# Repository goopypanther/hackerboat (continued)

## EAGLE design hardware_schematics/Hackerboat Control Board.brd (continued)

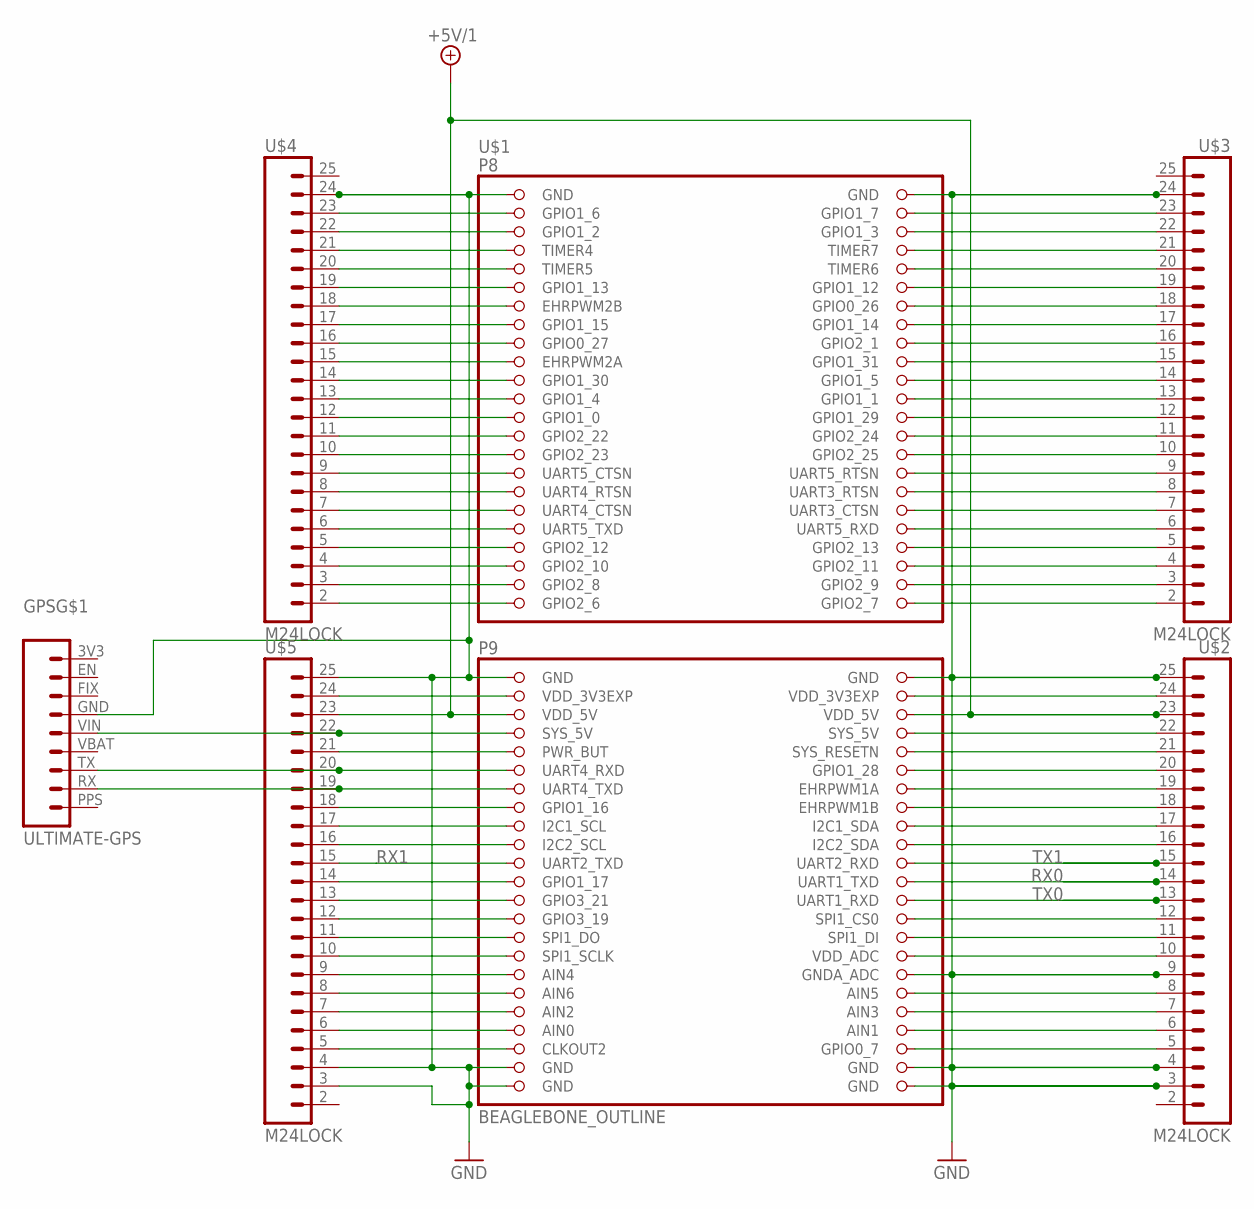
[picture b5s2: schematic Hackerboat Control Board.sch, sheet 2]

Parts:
GPS: ULTIMATE-GPS
U$1: BEAGLEBONE_OUTLINE; BEAGLEBONE_SHIELD
U$2, U$3, U$4, U$5: M24LOCK; 1X24_LOCK

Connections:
+5V/1: U$1.51 (VDD_5V), U$1.52 (VDD_5V), U$2.23, U$5.23; also elsewhere on the board
GND: GPS.GND (6), U$1.1 (GND), U$1.2 (GND), U$1.47 (GND), U$1.48 (GND), U$1.80 (GNDA_ADC), U$1.89 (GND), U$1.90 (GND), U$1.91 (GND), U$1.92 (GND), U$2.3, U$2.4, U$2.9, U$2.25, U$3.24, U$4.24, U$5.3, U$5.4, U$5.25; also elsewhere on the board
unnamed: GPS.RX (2), U$1.59 (UART4_TXD), U$5.19
unnamed: GPS.TX (3), U$1.57 (UART4_RXD), U$5.20
unnamed: GPS.VIN (5), U$1.53 (SYS_5V), U$5.22
unnamed: U$1.49 (VDD_3V3EXP), U$5.24
unnamed: U$1.88 (GPIO0_7), U$2.5
unnamed: U$1.86 (AIN1), U$2.6
unnamed: U$1.84 (AIN3), U$2.7
unnamed: U$1.82 (AIN5), U$2.8
unnamed: U$1.78 (VDD_ADC), U$2.10
unnamed: U$1.76 (SPI1_DI), U$2.11
unnamed: U$1.74 (SPI1_CS0), U$2.12
unnamed: U$1.66 (I2C2_SDA), U$2.16
unnamed: U$1.64 (I2C1_SDA), U$2.17
unnamed: U$1.62 (EHRPWM1B), U$2.18
unnamed: U$1.60 (EHRPWM1A), U$2.19
unnamed: U$1.58 (GPIO1_28), U$2.20
unnamed: U$1.56 (SYS_RESETN), U$2.21
unnamed: U$1.54 (SYS_5V), U$2.22
unnamed: U$1.50 (VDD_3V3EXP), U$2.24
unnamed: U$1.46 (GPIO2_7), U$3.2
unnamed: U$1.44 (GPIO2_9), U$3.3
unnamed: U$1.42 (GPIO2_11), U$3.4
unnamed: U$1.40 (GPIO2_13), U$3.5
unnamed: U$1.38 (UART5_RXD), U$3.6
unnamed: U$1.36 (UART3_CTSN), U$3.7
unnamed: U$1.34 (UART3_RTSN), U$3.8
unnamed: U$1.32 (UART5_RTSN), U$3.9
unnamed: U$1.30 (GPIO2_25), U$3.10
unnamed: U$1.28 (GPIO2_24), U$3.11
unnamed: U$1.26 (GPIO1_29), U$3.12
unnamed: U$1.24 (GPIO1_1), U$3.13
unnamed: U$1.22 (GPIO1_5), U$3.14
unnamed: U$1.20 (GPIO1_31), U$3.15
unnamed: U$1.18 (GPIO2_1), U$3.16
unnamed: U$1.16 (GPIO1_14), U$3.17
unnamed: U$1.14 (GPIO0_26), U$3.18
unnamed: U$1.12 (GPIO1_12), U$3.19
unnamed: U$1.10 (TIMER6), U$3.20
unnamed: U$1.8 (TIMER7), U$3.21
unnamed: U$1.6 (GPIO1_3), U$3.22
unnamed: U$1.4 (GPIO1_7), U$3.23
unnamed: U$1.45 (GPIO2_6), U$4.2
unnamed: U$1.43 (GPIO2_8), U$4.3
unnamed: U$1.41 (GPIO2_10), U$4.4
unnamed: U$1.39 (GPIO2_12), U$4.5
unnamed: U$1.37 (UART5_TXD), U$4.6
unnamed: U$1.35 (UART4_CTSN), U$4.7
unnamed: U$1.33 (UART4_RTSN), U$4.8
unnamed: U$1.31 (UART5_CTSN), U$4.9
unnamed: U$1.29 (GPIO2_23), U$4.10
unnamed: U$1.27 (GPIO2_22), U$4.11
unnamed: U$1.25 (GPIO1_0), U$4.12
unnamed: U$1.23 (GPIO1_4), U$4.13
unnamed: U$1.21 (GPIO1_30), U$4.14
unnamed: U$1.19 (EHRPWM2A), U$4.15
unnamed: U$1.17 (GPIO0_27), U$4.16
unnamed: U$1.15 (GPIO1_15), U$4.17
unnamed: U$1.13 (EHRPWM2B), U$4.18
unnamed: U$1.11 (GPIO1_13), U$4.19
unnamed: U$1.9 (TIMER5), U$4.20
unnamed: U$1.7 (TIMER4), U$4.21
unnamed: U$1.5 (GPIO1_2), U$4.22
unnamed: U$1.3 (GPIO1_6), U$4.23
unnamed: U$1.87 (CLKOUT2), U$5.5
unnamed: U$1.85 (AIN0), U$5.6
unnamed: U$1.83 (AIN2), U$5.7
unnamed: U$1.81 (AIN6), U$5.8
unnamed: U$1.79 (AIN4), U$5.9
unnamed: U$1.77 (SPI1_SCLK), U$5.10
unnamed: U$1.75 (SPI1_DO), U$5.11
unnamed: U$1.73 (GPIO3_19), U$5.12
unnamed: U$1.71 (GPIO3_21), U$5.13
unnamed: U$1.69 (GPIO1_17), U$5.14
unnamed: U$1.65 (I2C2_SCL), U$5.16
unnamed: U$1.63 (I2C1_SCL), U$5.17
unnamed: U$1.61 (GPIO1_16), U$5.18
unnamed: U$1.55 (PWR_BUT), U$5.21
RX0: U$1.70 (UART1_TXD), U$2.14; also elsewhere on the board
RX1: U$1.67 (UART2_TXD), U$5.15; also elsewhere on the board
TX0: U$1.72 (UART1_RXD), U$2.13; also elsewhere on the board
TX1: U$1.68 (UART2_RXD), U$2.15; also elsewhere on the board

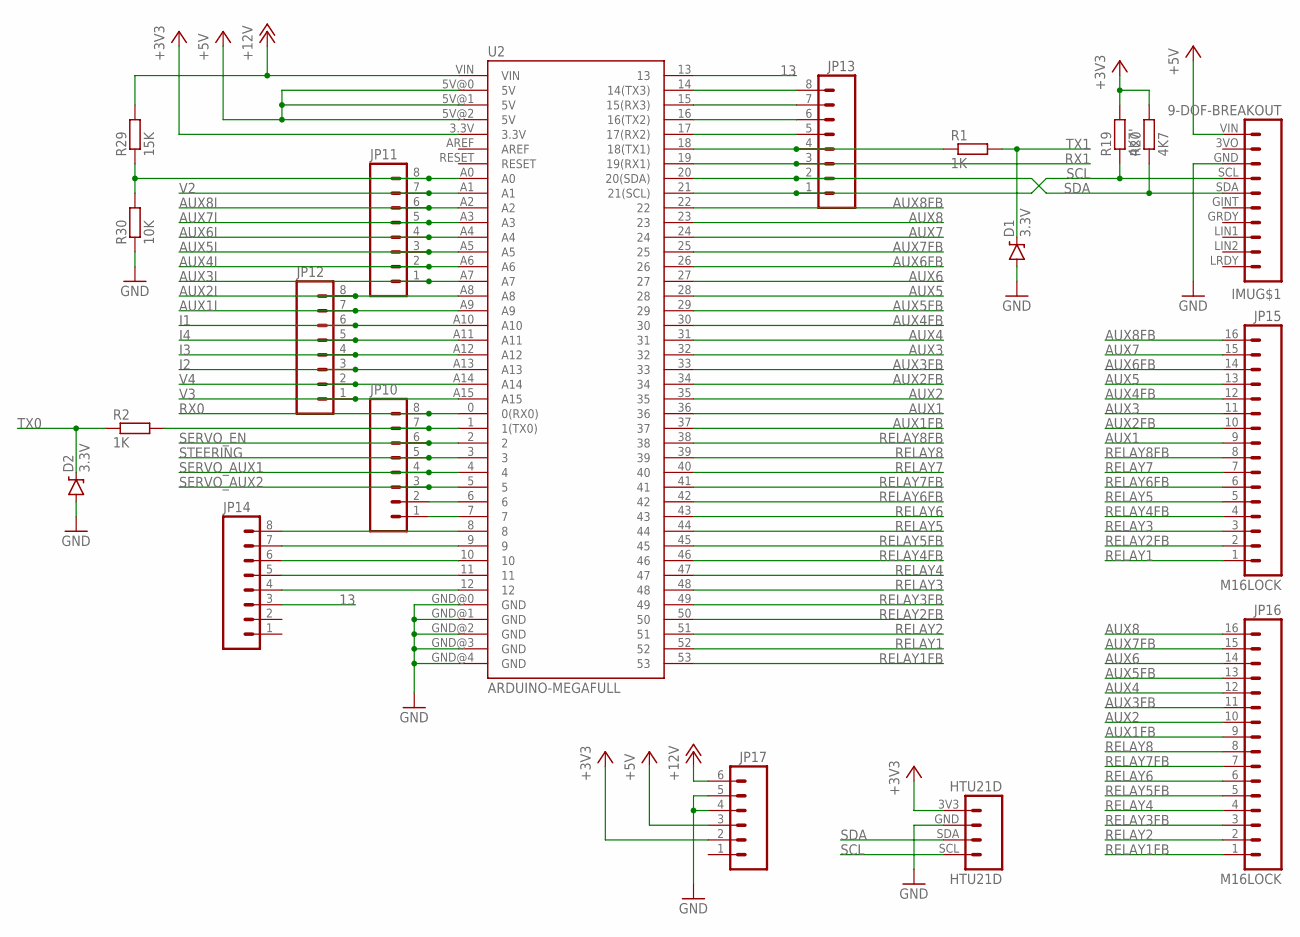
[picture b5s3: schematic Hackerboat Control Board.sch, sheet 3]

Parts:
D1, D2: 3.3V; SOD-323
HTU21D: HTU21D
IMU: 9-DOF-BREAKOUT
JP10, JP11, JP12, JP13, JP14: M08LOCK; 1X08_LOCK
JP15, JP16: M16LOCK; 1X16_LOCK
JP17: M06LOCK; 1X06_LOCK
R1, R2: 1K; R0603
R19: 4K7'; R0603
R20: 4K7; R0603
R29: 15K; R0603
R30: 10K; R0603
U2: ARDUINO-MEGAFULL; ARDUINO_MEGA

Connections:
13: JP14.3, U2.13
+3V3: HTU21D.3V3 (1), JP17.2, R19.2, R20.2, U2.3.3V
+5V: IMU.VIN (1), JP17.3, U2.5V@0 (5V), U2.5V@1 (5V), U2.5V@2 (5V); also elsewhere on the board
+12V: JP17.6, R29.2, U2.VIN; also elsewhere on the board
AUX1: JP15.9, U2.36; also elsewhere on the board
AUX1FB: JP16.9, U2.37; also elsewhere on the board
AUX1I: JP12.7, U2.A9; also elsewhere on the board
AUX2: JP16.10, U2.35; also elsewhere on the board
AUX2FB: JP15.10, U2.34; also elsewhere on the board
AUX2I: JP12.8, U2.A8; also elsewhere on the board
AUX3: JP15.11, U2.32; also elsewhere on the board
AUX3FB: JP16.11, U2.33; also elsewhere on the board
AUX3I: JP11.1, U2.A7; also elsewhere on the board
AUX4: JP16.12, U2.31; also elsewhere on the board
AUX4FB: JP15.12, U2.30; also elsewhere on the board
AUX4I: JP11.2, U2.A6; also elsewhere on the board
AUX5: JP15.13, U2.28; also elsewhere on the board
AUX5FB: JP16.13, U2.29; also elsewhere on the board
AUX5I: JP11.3, U2.A5; also elsewhere on the board
AUX6: JP16.14, U2.27; also elsewhere on the board
AUX6FB: JP15.14, U2.26; also elsewhere on the board
AUX6I: JP11.4, U2.A4; also elsewhere on the board
AUX7: JP15.15, U2.24; also elsewhere on the board
AUX7FB: JP16.15, U2.25; also elsewhere on the board
AUX7I: JP11.5, U2.A3; also elsewhere on the board
AUX8: JP16.16, U2.23; also elsewhere on the board
AUX8FB: JP15.16, U2.22; also elsewhere on the board
AUX8I: JP11.6, U2.A2; also elsewhere on the board
GND: D1.A, D2.A, HTU21D.GND (2), IMU.GND (3), JP17.4, JP17.5, R30.1, U2.GND@0 (GND), U2.GND@1 (GND), U2.GND@2 (GND), U2.GND@3 (GND), U2.GND@4 (GND); also elsewhere on the board
I1: JP12.6, U2.A10; also elsewhere on the board
I2: JP12.3, U2.A13; also elsewhere on the board
I3: JP12.4, U2.A12; also elsewhere on the board
I4: JP12.5, U2.A11; also elsewhere on the board
unnamed: JP13.4, R1.1, U2.18 (18(TX1))
unnamed: JP10.7, R2.2, U2.1 (1(TX0))
unnamed: JP10.1, U2.7
unnamed: JP10.2, U2.6
unnamed: JP11.8, R29.1, R30.2, U2.A0
unnamed: JP13.5, U2.17 (17(RX2))
unnamed: JP13.6, U2.16 (16(TX2))
unnamed: JP13.7, U2.15 (15(RX3))
unnamed: JP13.8, U2.14 (14(TX3))
unnamed: JP14.8, U2.8
unnamed: JP14.7, U2.9
unnamed: JP14.6, U2.10
unnamed: JP14.5, U2.11
unnamed: JP14.4, U2.12
RELAY1: JP15.1, U2.52; also elsewhere on the board
RELAY1FB: JP16.1, U2.53; also elsewhere on the board
RELAY2: JP16.2, U2.51; also elsewhere on the board
RELAY2FB: JP15.2, U2.50; also elsewhere on the board
RELAY3: JP15.3, U2.48; also elsewhere on the board
RELAY3FB: JP16.3, U2.49; also elsewhere on the board
RELAY4: JP16.4, U2.47; also elsewhere on the board
RELAY4FB: JP15.4, U2.46; also elsewhere on the board
RELAY5: JP15.5, U2.44; also elsewhere on the board
RELAY5FB: JP16.5, U2.45; also elsewhere on the board
RELAY6: JP16.6, U2.43; also elsewhere on the board
RELAY6FB: JP15.6, U2.42; also elsewhere on the board
RELAY7: JP15.7, U2.40; also elsewhere on the board
RELAY7FB: JP16.7, U2.41; also elsewhere on the board
RELAY8: JP16.8, U2.39; also elsewhere on the board
RELAY8FB: JP15.8, U2.38; also elsewhere on the board
RX0: JP10.8, U2.0 (0(RX0)); also elsewhere on the board
RX1: JP13.3, U2.19 (19(RX1)); also elsewhere on the board
SCL: HTU21D.SCL (4), IMU.SCL (4), JP13.1, R19.1, U2.21 (21(SCL))
SDA: HTU21D.SDA (3), IMU.SDA (5), JP13.2, R20.1, U2.20 (20(SDA))
SERVO_AUX1: JP10.4, U2.4; also elsewhere on the board
SERVO_AUX2: JP10.3, U2.5; also elsewhere on the board
SERVO_EN: JP10.6, U2.2; also elsewhere on the board
STEERING: JP10.5, U2.3; also elsewhere on the board
TX0: D2.C, R2.1; also elsewhere on the board
TX1: D1.C, R1.2; also elsewhere on the board
V2: JP11.7, U2.A1; also elsewhere on the board
V3: JP12.1, U2.A15; also elsewhere on the board
V4: JP12.2, U2.A14; also elsewhere on the board

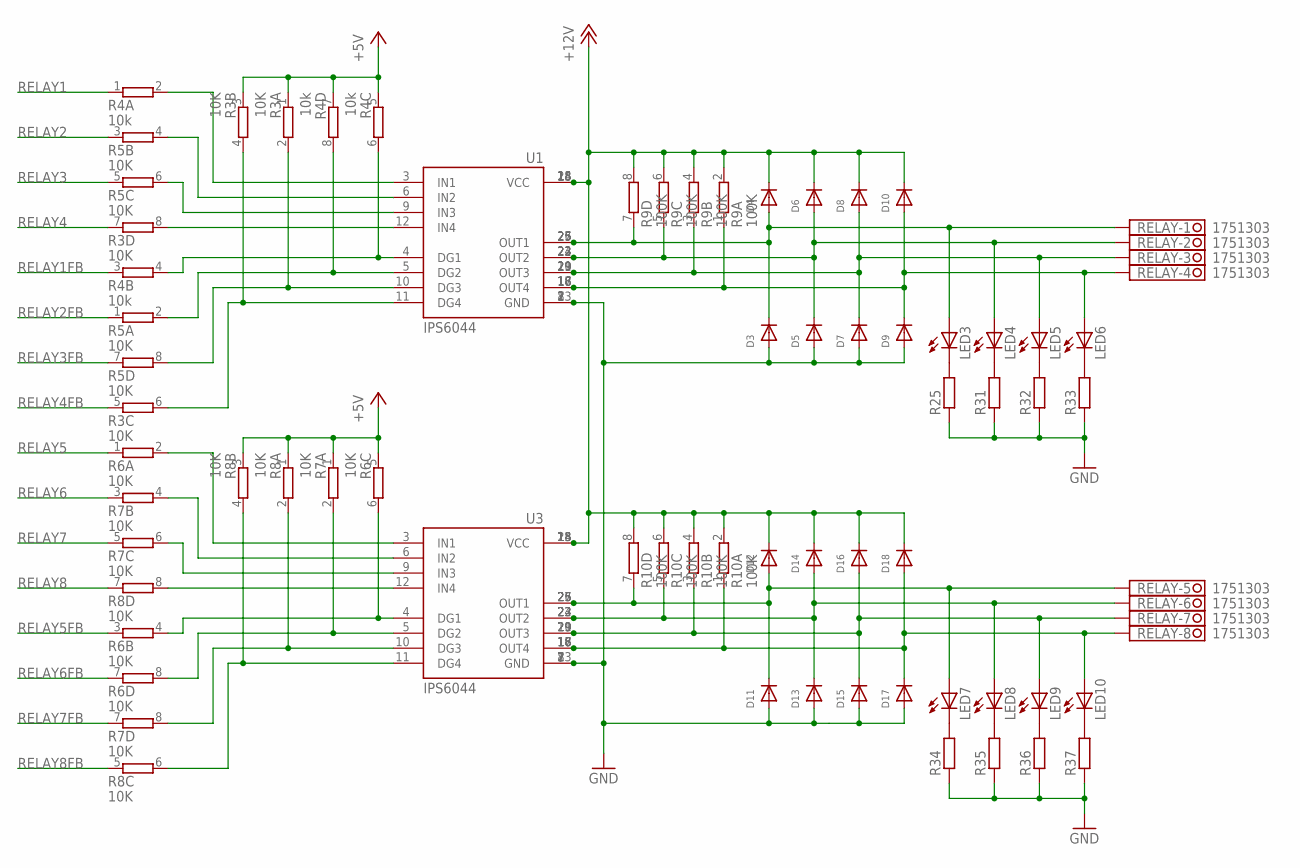
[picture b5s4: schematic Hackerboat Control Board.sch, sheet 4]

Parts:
D3, D4, D5, D6, D7, D8, D9, D10, D11, D12, D13, D14, D15, D16, D17, D18: DIODESOD-123; SOD-123
LED3, LED4, LED5, LED6, LED7, LED8, LED9, LED10: LEDCHIPLED_0805; CHIPLED_0805
R3, R5, R6, R7, R8: 10K; CTS742C083-RES
R4: 10k; CTS742C083-RES
R9, R10: 100K; CTS742C083-RES
R25, R31, R32, R33, R34, R35, R36, R37: R-EU_R0603; R0603
RELAY: 1751303
U1, U3: IPS6044; SO-28L

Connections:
+5V: R3.1, R3.3 (1), R4.5 (1), R4.7 (1), R6.5 (1), R7.1, R8.1, R8.3 (1); also elsewhere on the board
+12V: D4.C, D6.C, D8.C, D10.C, D12.C, D14.C, D16.C, D18.C, R9.2, R9.4 (2), R9.6 (2), R9.8 (2), R10.2, R10.4 (2), R10.6 (2), R10.8 (2), U1.1 (VCC), U1.14 (VCC), U1.15 (VCC), U1.28 (VCC), U3.1 (VCC), U3.14 (VCC), U3.15 (VCC), U3.28 (VCC); also elsewhere on the board
GND: D3.A, D5.A, D7.A, D9.A, D11.A, D13.A, D15.A, D17.A, R25.1, R31.1, R32.1, R33.1, R34.1, R35.1, R36.1, R37.1, U1.2 (GND), U1.7 (GND), U1.8 (GND), U1.13 (GND), U3.2 (GND), U3.7 (GND), U3.8 (GND), U3.13 (GND); also elsewhere on the board
unnamed: R6.2, U3.3 (IN1)
unnamed: R8.8 (2), U3.12 (IN4)
unnamed: R7.6 (2), U3.9 (IN3)
unnamed: D3.C, D4.A, LED3.A, R9.7 (1), RELAY.1, U1.25 (OUT1), U1.26 (OUT1), U1.27 (OUT1)
unnamed: D5.C, D6.A, LED4.A, R9.5 (1), RELAY.2, U1.22 (OUT2), U1.23 (OUT2), U1.24 (OUT2)
unnamed: D7.C, D8.A, LED5.A, R9.3 (1), RELAY.3, U1.19 (OUT3), U1.20 (OUT3), U1.21 (OUT3)
unnamed: D9.C, D10.A, LED6.A, R9.1, RELAY.4, U1.16 (OUT4), U1.17 (OUT4), U1.18 (OUT4)
unnamed: R4.2, U1.3 (IN1)
unnamed: R5.4 (2), U1.6 (IN2)
unnamed: R5.6 (2), U1.9 (IN3)
unnamed: R3.8 (2), U1.12 (IN4)
unnamed: R4.4 (2), R4.6 (2), U1.4 (DG1)
unnamed: R4.8 (2), R5.2, U1.5 (DG2)
unnamed: R3.2, R5.8 (2), U1.10 (DG3)
unnamed: R3.4 (2), R3.6 (2), U1.11 (DG4)
unnamed: R7.4 (2), U3.6 (IN2)
unnamed: R6.8 (2), R7.2, U3.5 (DG2)
unnamed: R6.4 (2), R6.6 (2), U3.4 (DG1)
unnamed: R7.8 (2), R8.2, U3.10 (DG3)
unnamed: R8.4 (2), R8.6 (2), U3.11 (DG4)
unnamed: D11.C, D12.A, LED7.A, R10.7 (1), RELAY.5, U3.25 (OUT1), U3.26 (OUT1), U3.27 (OUT1)
unnamed: D13.C, D14.A, LED8.A, R10.5 (1), RELAY.6, U3.22 (OUT2), U3.23 (OUT2), U3.24 (OUT2)
unnamed: D15.C, D16.A, LED9.A, R10.3 (1), RELAY.7, U3.19 (OUT3), U3.20 (OUT3), U3.21 (OUT3)
unnamed: D17.C, D18.A, LED10.A, R10.1, RELAY.8, U3.16 (OUT4), U3.17 (OUT4), U3.18 (OUT4)
unnamed: LED3.C, R25.2
unnamed: LED4.C, R31.2
unnamed: LED5.C, R32.2
unnamed: LED6.C, R33.2
unnamed: LED7.C, R34.2
unnamed: LED8.C, R35.2
unnamed: LED9.C, R36.2
unnamed: LED10.C, R37.2
RELAY1: R4.1; also elsewhere on the board
RELAY1FB: R4.3 (1); also elsewhere on the board
RELAY2: R5.3 (1); also elsewhere on the board
RELAY2FB: R5.1; also elsewhere on the board
RELAY3: R5.5 (1); also elsewhere on the board
RELAY3FB: R5.7 (1); also elsewhere on the board
RELAY4: R3.7 (1); also elsewhere on the board
RELAY4FB: R3.5 (1); also elsewhere on the board
RELAY5: R6.1; also elsewhere on the board
RELAY5FB: R6.3 (1); also elsewhere on the board
RELAY6: R7.3 (1); also elsewhere on the board
RELAY6FB: R6.7 (1); also elsewhere on the board
RELAY7: R7.5 (1); also elsewhere on the board
RELAY7FB: R7.7 (1); also elsewhere on the board
RELAY8: R8.7 (1); also elsewhere on the board
RELAY8FB: R8.5 (1); also elsewhere on the board

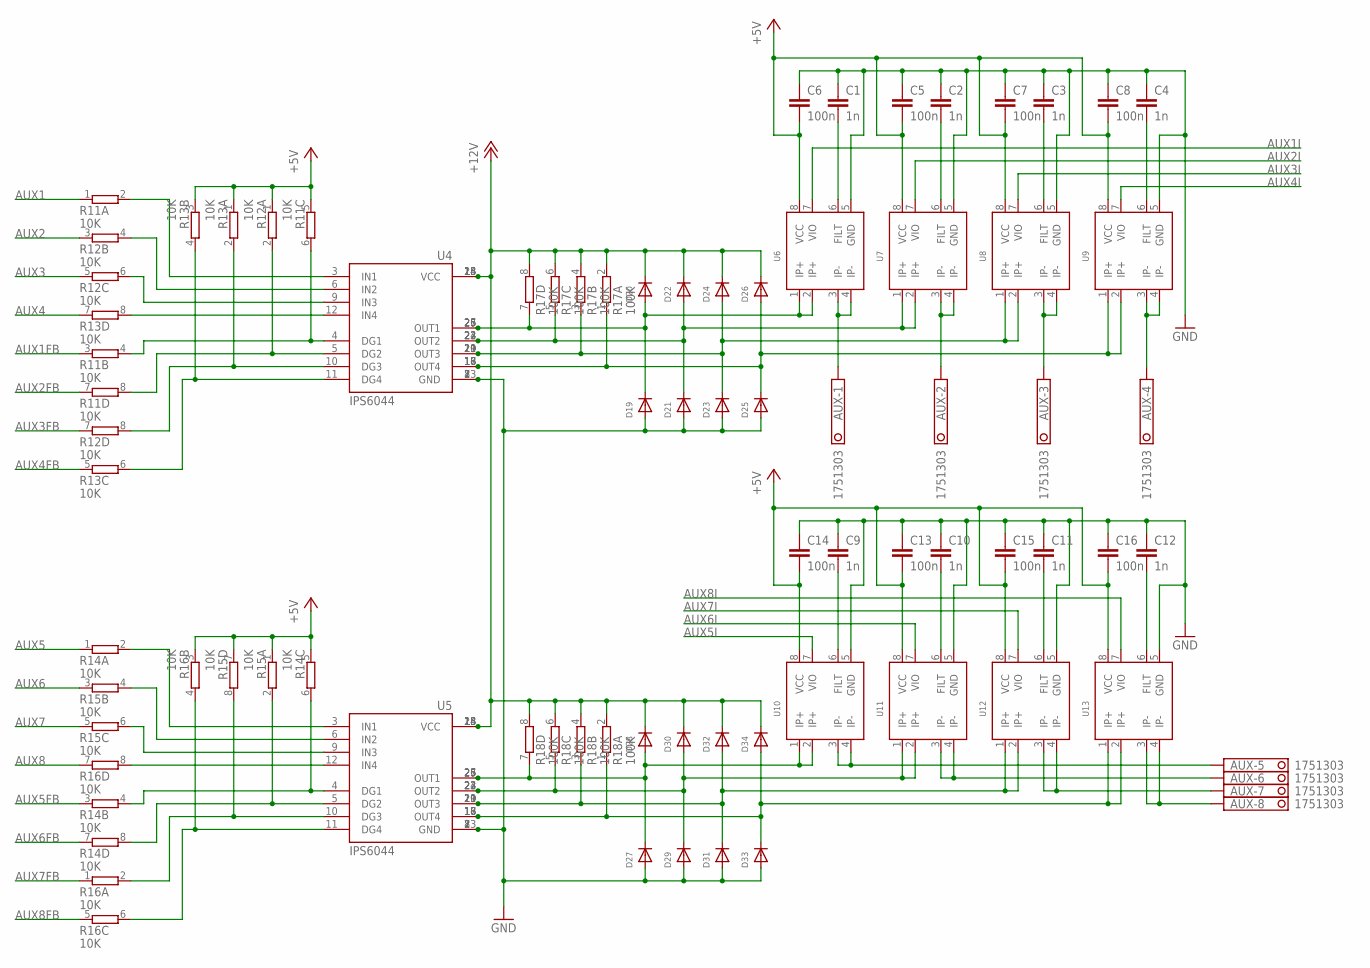
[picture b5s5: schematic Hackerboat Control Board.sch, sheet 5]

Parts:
AUX: 1751303
C1, C2, C3, C4, C9, C10, C11, C12: 1n; C0603
C5, C6, C7, C8, C13, C14, C15, C16: 100n; C0603
D19, D20, D21, D22, D23, D24, D25, D26, D27, D28, D29, D30, D31, D32, D33, D34: DIODESOD-123; SOD-123
R11, R12, R13, R14, R15, R16: 10K; CTS742C083-RES
R17, R18: 100K; CTS742C083-RES
U4, U5: IPS6044; SO-28L
U6, U7, U8, U9, U10, U11, U12, U13: ACS712; SO08

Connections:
+5V: C5.2, C6.2, C7.2, C8.2, C13.2, C14.2, C15.2, C16.2, R11.5 (1), R12.1, R13.1, R13.3 (1), R14.5 (1), R15.1, R15.7 (1), R16.3 (1), U6.8 (VCC), U7.8 (VCC), U8.8 (VCC), U9.8 (VCC), U10.8 (VCC), U11.8 (VCC), U12.8 (VCC), U13.8 (VCC); also elsewhere on the board
+12V: D20.C, D22.C, D24.C, D26.C, D28.C, D30.C, D32.C, D34.C, R17.2, R17.4 (2), R17.6 (2), R17.8 (2), R18.2, R18.4 (2), R18.6 (2), R18.8 (2), U4.1 (VCC), U4.14 (VCC), U4.15 (VCC), U4.28 (VCC), U5.1 (VCC), U5.14 (VCC), U5.15 (VCC), U5.28 (VCC); also elsewhere on the board
AUX1: R11.1; also elsewhere on the board
AUX1FB: R11.3 (1); also elsewhere on the board
AUX1I: U6.7 (VIO); also elsewhere on the board
AUX2: R12.3 (1); also elsewhere on the board
AUX2FB: R11.7 (1); also elsewhere on the board
AUX2I: U7.7 (VIO); also elsewhere on the board
AUX3: R12.5 (1); also elsewhere on the board
AUX3FB: R12.7 (1); also elsewhere on the board
AUX3I: U8.7 (VIO); also elsewhere on the board
AUX4: R13.7 (1); also elsewhere on the board
AUX4FB: R13.5 (1); also elsewhere on the board
AUX4I: U9.7 (VIO); also elsewhere on the board
AUX5: R14.1; also elsewhere on the board
AUX5FB: R14.3 (1); also elsewhere on the board
AUX5I: U10.7 (VIO); also elsewhere on the board
AUX6: R15.3 (1); also elsewhere on the board
AUX6FB: R14.7 (1); also elsewhere on the board
AUX6I: U11.7 (VIO); also elsewhere on the board
AUX7: R15.5 (1); also elsewhere on the board
AUX7FB: R16.1; also elsewhere on the board
AUX7I: U12.7 (VIO); also elsewhere on the board
AUX8: R16.7 (1); also elsewhere on the board
AUX8FB: R16.5 (1); also elsewhere on the board
AUX8I: U13.7 (VIO); also elsewhere on the board
GND: C1.1, C2.1, C3.1, C4.1, C5.1, C6.1, C7.1, C8.1, C9.1, C10.1, C11.1, C12.1, C13.1, C14.1, C15.1, C16.1, D19.A, D21.A, D23.A, D25.A, D27.A, D29.A, D31.A, D33.A, U4.2 (GND), U4.7 (GND), U4.8 (GND), U4.13 (GND), U5.2 (GND), U5.7 (GND), U5.8 (GND), U5.13 (GND), U6.5 (GND), U7.5 (GND), U8.5 (GND), U9.5 (GND), U10.5 (GND), U11.5 (GND), U12.5 (GND), U13.5 (GND); also elsewhere on the board
unnamed: D25.C, D26.A, R17.1, U4.16 (OUT4), U4.17 (OUT4), U4.18 (OUT4), U9.1 (IP+), U9.2 (IP+)
unnamed: AUX.2, U7.3 (IP-), U7.4 (IP-)
unnamed: AUX.3, U8.3 (IP-), U8.4 (IP-)
unnamed: AUX.4, U9.3 (IP-), U9.4 (IP-)
unnamed: AUX.5, U10.3 (IP-), U10.4 (IP-)
unnamed: D19.C, D20.A, R17.7 (1), U4.25 (OUT1), U4.26 (OUT1), U4.27 (OUT1), U6.1 (IP+), U6.2 (IP+)
unnamed: D21.C, D22.A, R17.5 (1), U4.22 (OUT2), U4.23 (OUT2), U4.24 (OUT2), U7.1 (IP+), U7.2 (IP+)
unnamed: D23.C, D24.A, R17.3 (1), U4.19 (OUT3), U4.20 (OUT3), U4.21 (OUT3), U8.1 (IP+), U8.2 (IP+)
unnamed: AUX.1, U6.3 (IP-), U6.4 (IP-)
unnamed: R11.2, U4.3 (IN1)
unnamed: R12.4 (2), U4.6 (IN2)
unnamed: R12.6 (2), U4.9 (IN3)
unnamed: R13.8 (2), U4.12 (IN4)
unnamed: R11.4 (2), R11.6 (2), U4.4 (DG1)
unnamed: R11.8 (2), R12.2, U4.5 (DG2)
unnamed: R12.8 (2), R13.2, U4.10 (DG3)
unnamed: R13.4 (2), R13.6 (2), U4.11 (DG4)
unnamed: R14.2, U5.3 (IN1)
unnamed: R16.8 (2), U5.12 (IN4)
unnamed: R15.6 (2), U5.9 (IN3)
unnamed: R15.4 (2), U5.6 (IN2)
unnamed: R14.4 (2), R14.6 (2), U5.4 (DG1)
unnamed: R14.8 (2), R15.2, U5.5 (DG2)
unnamed: R15.8 (2), R16.2, U5.10 (DG3)
unnamed: R16.4 (2), R16.6 (2), U5.11 (DG4)
unnamed: D27.C, D28.A, R18.7 (1), U5.25 (OUT1), U5.26 (OUT1), U5.27 (OUT1), U10.1 (IP+), U10.2 (IP+)
unnamed: D29.C, D30.A, R18.5 (1), U5.22 (OUT2), U5.23 (OUT2), U5.24 (OUT2), U11.1 (IP+), U11.2 (IP+)
unnamed: D31.C, D32.A, R18.3 (1), U5.19 (OUT3), U5.20 (OUT3), U5.21 (OUT3), U12.1 (IP+), U12.2 (IP+)
unnamed: D33.C, D34.A, R18.1, U5.16 (OUT4), U5.17 (OUT4), U5.18 (OUT4), U13.1 (IP+), U13.2 (IP+)
unnamed: AUX.6, U11.3 (IP-), U11.4 (IP-)
unnamed: AUX.7, U12.3 (IP-), U12.4 (IP-)
unnamed: AUX.8, U13.3 (IP-), U13.4 (IP-)
unnamed: C1.2, U6.6 (FILT)
unnamed: C2.2, U7.6 (FILT)
unnamed: C3.2, U8.6 (FILT)
unnamed: C4.2, U9.6 (FILT)
unnamed: C9.2, U10.6 (FILT)
unnamed: C10.2, U11.6 (FILT)
unnamed: C11.2, U12.6 (FILT)
unnamed: C12.2, U13.6 (FILT)

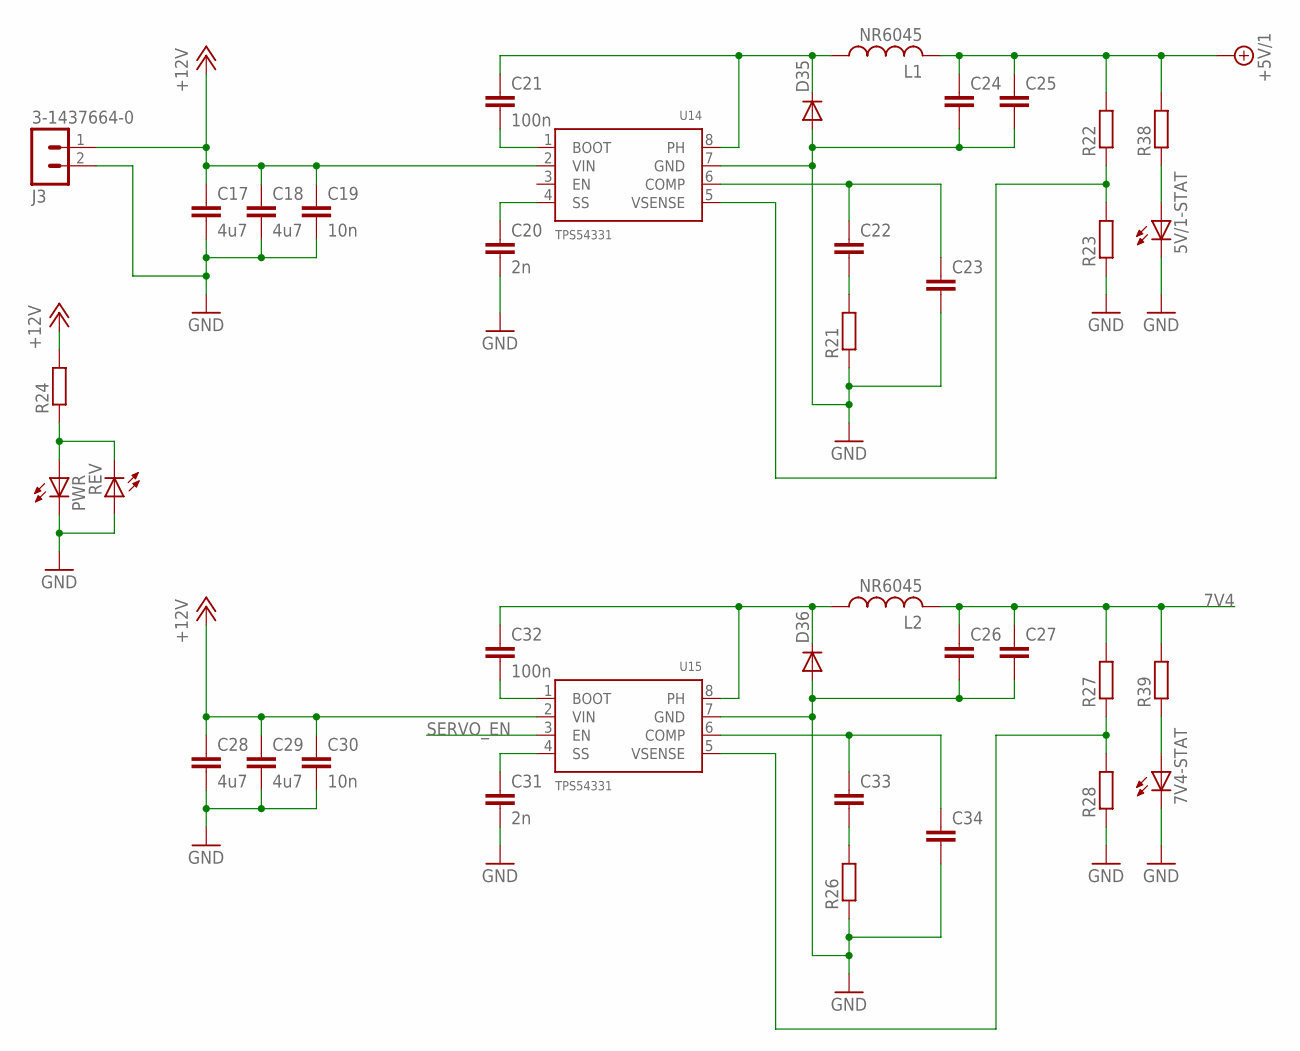
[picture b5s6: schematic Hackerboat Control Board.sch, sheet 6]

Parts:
5V/1-STAT, 7V4-STAT: LEDCHIPLED_0805; CHIPLED_0805
C17, C18, C28, C29: 4u7; C1210
C19, C30: 10n; C0603
C20, C31: 2n; C0603
C21, C32: 100n; C0603
C22, C23, C33, C34: C-EUC0603; C0603
C24, C25, C26, C27: C-EUC1210; C1210
D35, D36: SPARKFUN_DIODESMA; SPARKFUN_SMA-DIODE
J3: 3-1437664-0; CONN-2
L1, L2: NR6045; NR60XX
PWR: LEDCHIPLED_0805; CHIPLED_0805
R21, R22, R23, R24, R26, R27, R28, R38, R39: R-EU_R0603; R0603
REV: LEDCHIPLED_0805; CHIPLED_0805
U14, U15: TPS54331; SO08

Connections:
7V4: C26.1, C27.1, L2.2, R27.2, R39.2; also elsewhere on the board
+5V/1: C24.1, C25.1, L1.2, R22.2, R38.2; also elsewhere on the board
+12V: C17.1, C18.1, C19.1, C28.1, C29.1, C30.1, J3.1, R24.2, U14.2 (VIN), U15.2 (VIN); also elsewhere on the board
GND: 5V/1-STAT.C, 7V4-STAT.C, C17.2, C18.2, C19.2, C20.2, C23.2, C24.2, C25.2, C26.2, C27.2, C28.2, C29.2, C30.2, C31.2, C34.2, D35.A, D36.A, J3.2, PWR.C, R21.1, R23.1, R26.1, R28.1, REV.A, U14.7 (GND), U15.7 (GND); also elsewhere on the board
unnamed: C21.2, U14.1 (BOOT)
unnamed: C21.1, D35.C, L1.1, U14.8 (PH)
unnamed: C22.2, R21.2
unnamed: C20.1, U14.4 (SS)
unnamed: C22.1, C23.1, U14.6 (COMP)
unnamed: C31.1, U15.4 (SS)
unnamed: R22.1, R23.2, U14.5 (VSENSE)
unnamed: C32.2, U15.1 (BOOT)
unnamed: C32.1, D36.C, L2.1, U15.8 (PH)
unnamed: C33.2, R26.2
unnamed: C33.1, C34.1, U15.6 (COMP)
unnamed: R27.1, R28.2, U15.5 (VSENSE)
unnamed: PWR.A, R24.1, REV.C
unnamed: 5V/1-STAT.A, R38.1
unnamed: 7V4-STAT.A, R39.1
SERVO_EN: U15.3 (EN); also elsewhere on the board

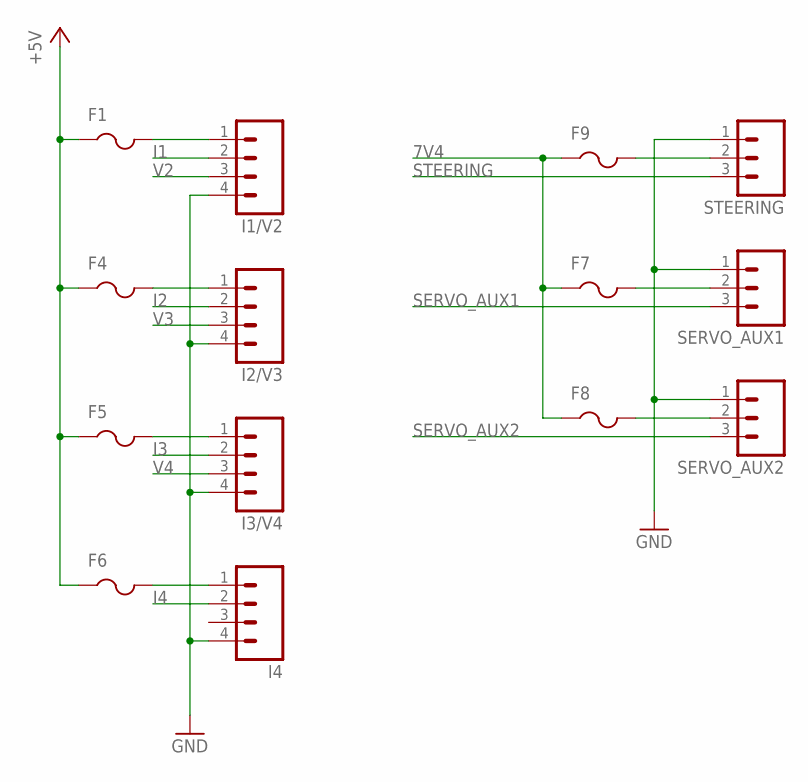
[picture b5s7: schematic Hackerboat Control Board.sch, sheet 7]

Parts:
F1, F4, F5, F6, F7, F8, F9: PTCFUSE-1206; R1206
I1/V2, I2/V3, I3/V4, I4: M04LOCK_LONGPADS; 1X04_LOCK_LONGPADS
SERVO_AUX1, SERVO_AUX2: M03LOCK_LONGPADS; 1X03_LOCK_LONGPADS
STEERING: M03LOCK_LONGPADS; 1X03_LOCK_LONGPADS

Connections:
7V4: F7.1, F8.1, F9.1; also elsewhere on the board
+5V: F1.1, F4.1, F5.1, F6.1; also elsewhere on the board
GND: I1/V2.4, I2/V3.4, I3/V4.4, I4.4, SERVO_AUX1.1, SERVO_AUX2.1, STEERING.1; also elsewhere on the board
I1: I1/V2.2; also elsewhere on the board
I2: I2/V3.2; also elsewhere on the board
I3: I3/V4.2; also elsewhere on the board
I4: I4.2; also elsewhere on the board
unnamed: F1.2, I1/V2.1
unnamed: F4.2, I2/V3.1
unnamed: F5.2, I3/V4.1
unnamed: F6.2, I4.1
unnamed: F7.2, SERVO_AUX1.2
unnamed: F8.2, SERVO_AUX2.2
unnamed: F9.2, STEERING.2
SERVO_AUX1: SERVO_AUX1.3; also elsewhere on the board
SERVO_AUX2: SERVO_AUX2.3; also elsewhere on the board
STEERING: STEERING.3; also elsewhere on the board
V2: I1/V2.3; also elsewhere on the board
V3: I2/V3.3; also elsewhere on the board
V4: I3/V4.3; also elsewhere on the board

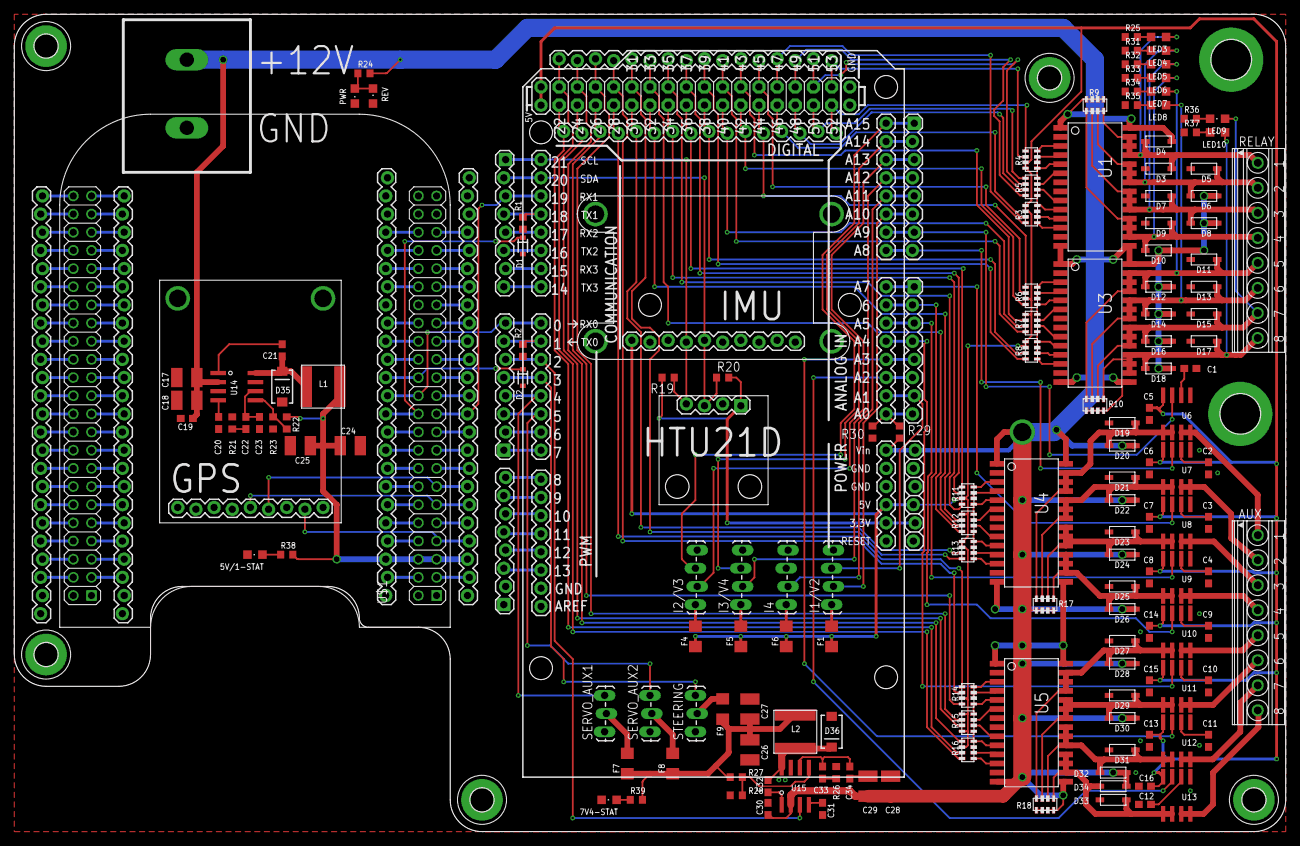
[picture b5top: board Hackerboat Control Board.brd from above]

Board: 2 copper layers, 177.8 x 114.3 mm, 178 parts (0 on the bottom side), 249 nets.
